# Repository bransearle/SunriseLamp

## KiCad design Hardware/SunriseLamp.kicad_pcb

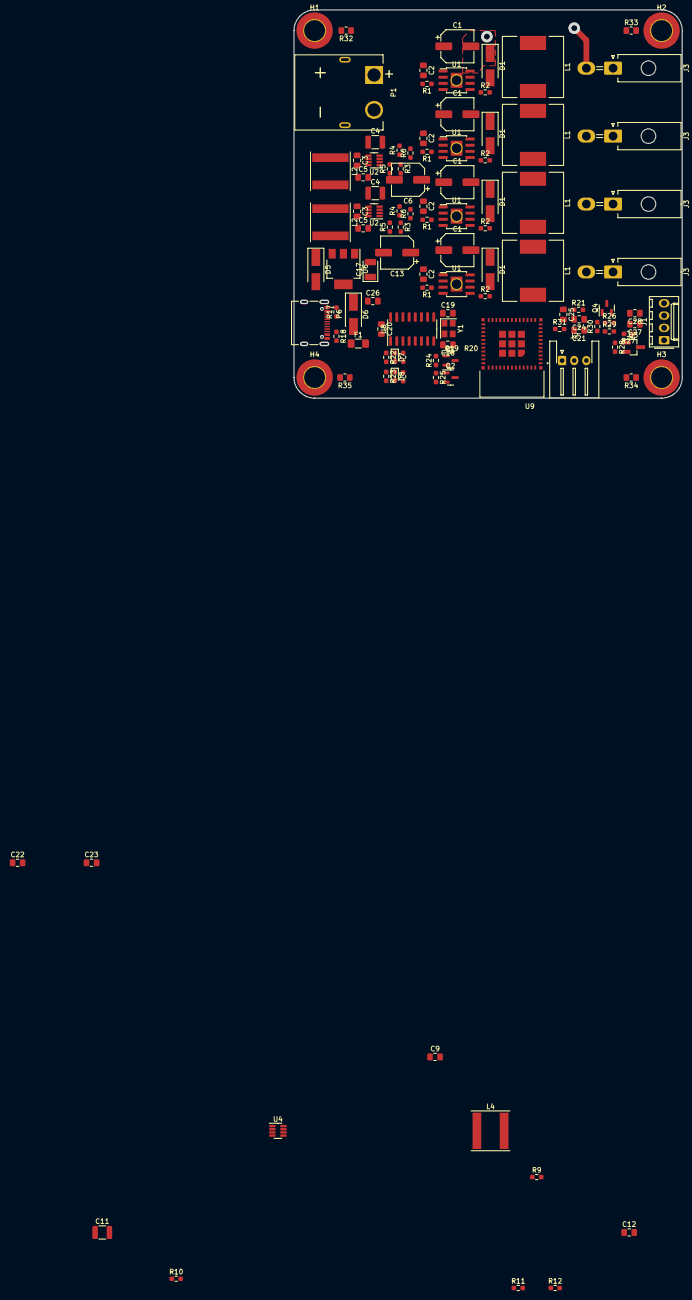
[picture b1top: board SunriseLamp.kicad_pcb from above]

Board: 4 copper layers, 80.0 x 80.0 mm, 113 parts (0 on the bottom side), 49 nets.

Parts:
C1, C1#2, C1#3, C1#4: 2u2 100V; CP_Elec_6.3x5.4
C2, C2#2, C2#3, C2#4: 1u 16V; C_0805_2012Metric_Pad1.18x1.45mm_HandSolder
C3, C3#2, C9: 10nF 50V; C_0805_2012Metric_Pad1.18x1.45mm_HandSolder
C4, C4#2, C11: 4u7 100V; C_1210_3225Metric
C5, C5#2, C12, C26: 10u 25V; C_0805_2012Metric_Pad1.18x1.45mm_HandSolder
C6, C13: 47u 25V; CP_Elec_6.3x5.4
C17: 22u TANT; CP_EIA-3528-15_AVX-H
C18, C19: 22p; C_0805_2012Metric_Pad1.18x1.45mm_HandSolder
C20, C22, C24, C25, C27: 100n; C_0805_2012Metric_Pad1.18x1.45mm_HandSolder
C21, C28: 1u; C_0805_2012Metric_Pad1.18x1.45mm_HandSolder
C23: 22u; C_0805_2012Metric_Pad1.18x1.45mm_HandSolder
D1, D1#2, D1#3, D1#4: SS310; D_SMA_Handsoldering
D5, D6: SS34; D_SMA_Handsoldering
D7: GREEN; LED_0603_1608Metric_Pad1.05x0.95mm_HandSolder
D8: RED; LED_0603_1608Metric_Pad1.05x0.95mm_HandSolder
F1: 0ZCJ0050FF2G; Fuse_1206_3216Metric_Pad1.42x1.75mm_HandSolder
H1, H2, H3, H4: 4.3mm; MountingHole_4.3mm_M4_DIN965_Pad_TopBottom
J1: Molex 047053-1000; Molex_KK-254_AE-6410-04A_1x04_P2.54mm_Vertical
J2: S3B-XH-A; JST_XH_S3B-XH-A-1_1x03_P2.50mm_Horizontal
J3, J3#2, J3#3, J3#4: Molex 26013114; Molex_Mini-Fit_Jr_5569-02A2_2x01_P4.20mm_Horizontal
L1, L1#2, L1#3, L1#4: 33u 2A; L_12x12mm_H6mm
L2, L2#2: 20uH >1.2A; L_Taiyo-Yuden_NR-80xx
L4: 20uH >0.5A; L_Taiyo-Yuden_NR-80xx
P1: XT60PW-M; AMASS_XT60PW-M
P6: TYPE-C-31-M-12; Korean_HRO_Type-C-31-M-12
Q1, Q2, Q4: MMBT3904; SOT-23
Q3: PMV16XNR; SOT-23_Handsoldering
R1, R1#2, R1#3, R1#4, R20: 3k3; R_0603_1608Metric_Pad0.98x0.95mm_HandSolder
R2, R2#2, R2#3, R2#4: 20k; R_0603_1608Metric_Pad0.98x0.95mm_HandSolder
R3, R3#2, R5, R5#2, R9, R10: 100k; R_0603_1608Metric_Pad0.98x0.95mm_HandSolder
R4, R4#2, R19, R30, R31: 4k7; R_0603_1608Metric_Pad0.98x0.95mm_HandSolder
R6, R6#2: 560R; R_0603_1608Metric_Pad0.98x0.95mm_HandSolder
R11: 33k; R_0603_1608Metric_Pad0.98x0.95mm_HandSolder
R12: 22k; R_0603_1608Metric_Pad0.98x0.95mm_HandSolder
R17, R18: 5k1; R_0603_1608Metric_Pad0.98x0.95mm_HandSolder
R21, R24, R25, R28: 10k; R_0603_1608Metric_Pad0.98x0.95mm_HandSolder
R22, R23: 0R; R_0603_1608Metric_Pad0.98x0.95mm_HandSolder
R26: 2k7; R_0603_1608Metric_Pad0.98x0.95mm_HandSolder
R27: 1k; R_0603_1608Metric_Pad0.98x0.95mm_HandSolder
R29: NF; R_0603_1608Metric_Pad0.98x0.95mm_HandSolder
R32, R33, R34, R35: 0R; R_0805_2012Metric_Pad1.20x1.40mm_HandSolder
U1, U1#2, U1#3, U1#4: LM3414; TI_SO-PowerPAD-8_HandSolder
U2, U2#2, U4: SY8303; TSOT-23-8
U6: AMS1117-3.3; SOT-223-3_TabPin2
U8: CH340G; SOIC-16_3.9x9.9mm_P1.27mm
U9: ESP32-PICO-MINI-02
Y1: 12MHz; Crystal_SMD_3225-4Pin_3.2x2.5mm

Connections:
+3V3: C17.1, C20.1, C22.1, C23.1, D5.2 (A), J2.2, R19.1, R20.1, R21.1, R31.1, U6.2 (VO), U8.4 (V3), U8.16 (VCC), U9.3 (3V3)
+5V: C12.1, C13.1, C26.1, D5.1 (K), D6.1 (K), L4.2, R9.1, R26.1, R29.1, U6.3 (VI)
+12V: C5.1, C5#2.1, C6.1, C11.1, C27.1, C28.1, J1.2, L2.2, L2#2.2, R3.1, R3#2.1, U4.5 (VIN), U4.8 (EN)
+36V: C1.2, C1#2.2, C1#3.2, C1#4.2, C4.1, C4#2.1, D1.1 (K), D1#2.1 (K), D1#3.1 (K), D1#4.1 (K), J3.2, J3#2.2, J3#3.2, J3#4.2, P1.1 (+), U1.8 (VIN), U1#2.8 (VIN), U1#3.8 (VIN), U1#4.8 (VIN), U2.5 (VIN), U2.8 (EN), U2#2.5 (VIN), U2#2.8 (EN)
/IO-Control/USB-D+: P6.A6 (D+), U8.5 (UD+)
/IO-Control/USB-D-: P6.A7 (D-), U8.6 (UD-)
BOOT-MODE: C25.1, Q2.3 (C), U9.23 (IO0)
ENABLE: C21.1, C24.1, Q1.3 (C), R21.2, U9.8 (EN)
FAN-SENSE: J1.3, R26.2
GND: C1.1, C1#2.1, C1#3.1, C1#4.1, C2.2, C2#2.2, C2#3.2, C2#4.2, C4.2, C4#2.2, C5.2, C5#2.2, C6.2, C11.2, C12.2, C13.2, C17.2, C18.2, C19.2, C20.2, C21.2, C22.2, C23.2, C24.2, C25.2, C26.2, C27.2, C28.2, J2.1, P1.2 (-), P6.S1 (SHIELD), Q3.2 (S), Q4.2 (E), R1.2, R1#2.2, R1#3.2, R1#4.2, R2.2, R2#2.2, R2#3.2, R2#4.2, R5.1, R5#2.1, R6.2, R6#2.2, R10.1, R11.2, R12.2, R17.2, R18.2, R28.2, R32.1, R33.1, R34.1, R35.1, U1.2 (PGND), U1.4 (GND), U1.9 (PGDN), U1#2.2 (PGND), U1#2.4 (GND), U1#2.9 (PGDN), U1#3.2 (PGND), U1#3.4 (GND), U1#3.9 (PGDN), U1#4.2 (PGND), U1#4.4 (GND), U1#4.9 (PGDN), U2.3 (GND), U2.4 (GND), U2#2.3 (GND), U2#2.4 (GND), U4.3 (GND), U4.4 (GND), U6.1 (GND), U8.1 (GND), U9.1 (GND), U9.2 (GND), U9.11 (GND), U9.14 (GND), U9.36 (GND), U9.37 (GND), U9.38 (GND), U9.39 (GND), U9.40 (GND), U9.41 (GND), U9.42 (GND), U9.43 (GND), U9.44 (GND), U9.45 (GND), U9.46 (GND), U9.47 (GND), U9.48 (GND), U9.49 (GND), Y1.2, Y1.4
LED-RED-PWM: U1.6 (DIM), U1#2.6 (DIM), U1#3.6 (DIM), U1#4.6 (DIM)
unnamed: C2.1, C2#2.1, C2#3.1, C2#4.1, U1.1 (VCC), U1#2.1 (VCC), U1#3.1 (VCC), U1#4.1 (VCC)
unnamed: C3.1, C3#2.1, L2.1, L2#2.1, U2.6 (LX), U2#2.6 (LX)
unnamed: C3.2, C3#2.2, U2.7 (BOOST), U2#2.7 (BOOST)
unnamed: C9.1, L4.1, U4.6 (LX)
unnamed: C9.2, U4.7 (BOOST)
unnamed: C18.1, U8.7 (XI), Y1.1
unnamed: C19.1, U8.8 (XO), Y1.3
unnamed: D1.2 (A), D1#2.2 (A), D1#3.2 (A), D1#4.2 (A), L1.1, L1#2.1, L1#3.1, L1#4.1, U1.7 (LX), U1#2.7 (LX), U1#3.7 (LX), U1#4.7 (LX)
unnamed: D6.2 (A), F1.2
unnamed: D7.1 (K), R22.1, U8.2 (TXD)
unnamed: D7.2 (A), R19.2
unnamed: D8.1 (K), R23.1, U8.3 (RXD)
unnamed: D8.2 (A), R20.2
unnamed: H1.1, R32.2
unnamed: H2.1, R33.2
unnamed: H3.1, R34.2
unnamed: H4.1, R35.2
unnamed: J1.1, Q3.3 (D)
unnamed: J1.4, Q4.3 (C), R29.2
unnamed: J3.1, J3#2.1, J3#3.1, J3#4.1, L1.2, L1#2.2, L1#3.2, L1#4.2
unnamed: P6.A5 (CC), R17.1
unnamed: P6.B5 (VCONN), R18.1
unnamed: Q1.1 (B), R24.2
unnamed: Q2.1 (B), R25.2
unnamed: Q3.1 (G), R27.2, R28.1
unnamed: Q4.1 (B), R30.2
unnamed: R1.1, R1#2.1, R1#3.1, R1#4.1, U1.3 (IADJ), U1#2.3 (IADJ), U1#3.3 (IADJ), U1#4.3 (IADJ)
unnamed: R2.1, R2#2.1, R2#3.1, R2#4.1, U1.5 (FS), U1#2.5 (FS), U1#3.5 (FS), U1#4.5 (FS)
unnamed: R3.2, R3#2.2, R4.1, R4#2.1, U2.1 (FB), U2#2.1 (FB)
unnamed: R4.2, R4#2.2, R6.1, R6#2.1
unnamed: R5.2, R5#2.2, U2.2 (FS), U2#2.2 (FS)
unnamed: R10.2, U4.2 (FS)
unnamed: R9.2, R11.1, R12.1, U4.1 (FB)
TEMP-ONEWIRE: J2.3, R31.2
UART-DTR: Q2.2 (E), R24.1, U8.13 (~DTR)
UART-HOST-RX: R23.2, U9.31 (TXD0)
UART-HOST-TX: R22.2, U9.30 (RXD0)
UART-RTS: Q1.2 (E), R25.1, U8.14 (~RTS)

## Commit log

2022-05-15 Add gitignore for KiCad components
2022-05-15 Initial files & gitignore tweaks
2022-05-15 LED driver part values & labels on IO page
    Added the values (and some part numbers) for the LED drivers, and added some floating labels on the IO sheet to remind what still needs connecting.
2022-05-19 attempting CI run
2022-05-19 corrected, wrong machine
2022-05-19 creating dir, correcting artefact upload
2022-05-20 Trying to get files to upload
2022-05-20 Trying with KiBot example workflow
2022-05-20 Setting specific targets
2022-10-27 updating kibot config
2022-10-27 Most part assignents made, pending switch footprint & xtal selection
2022-10-28 Xtal footprint selected. Remaining parts need new footprints.
2022-10-28 USB footprint added, mount holes added.
2022-10-30 Whoops, acidentally wiped all part assignments somehow. corrected.
    Only pending footprint creation is for two switches.
2022-12-30 Layout changes
    Changed XT60 outputs to Mini-Fit Jr., laid out 80mm fan edge cuts, started positioning conns
2022-12-30 placement done, ESP32 footprint added
2022-12-30 adding back in 4th channel -- maybe still RGBW?
2022-12-30 removing white channel -- limited space on side of board from inductors
2022-12-30 white channel re-added to schem after full placement
2022-12-30 JLCPCB design rules added to project, layer designations set
2023-01-17 finally created part for pushbutton
2024-03-19 updated to new KiCAD format
